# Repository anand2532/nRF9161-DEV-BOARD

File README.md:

# nRF9161 UART Modem Module (v2)

A small 50 × 37.5 mm LTE-M / NB-IoT + GNSS modem board built around the Nordic **nRF9161**. Any host MCU controls it with AT commands over one 10-pin UART header.

> **Status:** v2 has passed DRC (0 errors, 0 unconnected), ERC (0 errors), schematic parity, an RF review and a DFM review. The JLCPCB fab and assembly package is in `fab/staging-v2-36d8578/`. **It has not been ordered yet.**

## Features

- **Nordic nRF9161-LACA-R7** SiP: LTE-M and NB-IoT, plus GNSS. (The nRF9161 has **no 2G/GSM**.)
- **Host interface on one header:** J20 is a 1×10, 2.54 mm header carrying UART with RTS/CTS, DTR wake, RI indicate and an open-drain reset.
- **Level-shifted host side:** SN74LXC translators referenced to the host's VIO (1.1–5.5 V per the LXC range), so 1.8 V, 3.3 V and 5 V hosts all work. If VIO is missing, the translators go hi-Z, so the board never back-powers the host.
- **Single supply:** VIN 3.0–5.5 V. It has reverse-polarity protection (SS34), a TVS (SMAJ5.0A), a 2 A fuse and ferrite filtering, plus a TLV73333 3.3 V LDO for the GPIO and translator rail.
- **nano-SIM (4FF)**, JAE SF72S006, with TPD3F303 ESD protection.
- **Two U.FL connectors:** LTE (J2) and GNSS (J5). The GNSS port supplies bias for an active antenna, switched by a TPS22919 from COEX0.
- **SWD:** 10-pin 1.27 mm Cortex debug header (J8), reset button SW2, and status LEDs (D3 power, D4 status/network).
- **Build:** 4-layer board, 1.6 mm, ENIG, parts on both sides (51 top / 16 bottom). Every part has an LCSC number for JLCPCB assembly.

## Block diagram

```mermaid
flowchart LR
  HOST["Host MCU<br/>(1.8 / 3.3 / 5 V)"] -- "J20: TX RX RTS CTS DTR RI" --> LS["SN74LXC2T45 ×2<br/>SN74LXC1T45 ×2<br/>(VIO ↔ 3.3 V)"]
  HOST -- "J20: nRESET" --> Q1["Q1 BSS138<br/>open-drain"]
  LS --> U1["nRF9161-LACA-R7<br/>LTE-M / NB-IoT / GNSS"]
  Q1 --> U1
  VIN["J20 VIN 3.0–5.5 V"] --> PROT["D1 SS34 · D2 SMAJ5.0A<br/>F1 2 A · FB4"] --> U1
  PROT --> LDO["U2 TLV73333<br/>3.3 V VDD_GPIO"] --> LS
  U1 -- "SIM_RST/CLK/IO/1V8" --> ESD["U4 TPD3F303"] --> SIM["J7 nano-SIM"]
  U1 -- "ANT" --> J2["J2 U.FL LTE"]
  U1 -- "GPS" --> J5["J5 U.FL GNSS"]
  LDO --> SW["U3 TPS22919<br/>(COEX0)"] -- "active-antenna bias" --> J5
  SWD["J8 SWD 2×5 1.27 mm"] --- U1
  U1 -- "P0.00" --> D4["D4 status / network LED"]
```

## Host header J20 pinout

| Pin | Name | Direction (host view) | Modem side |
|---|---|---|---|
| 1 | VIN | power in | 3.0–5.5 V supply |
| 2 | GND | — | ground |
| 3 | VIO | reference in | host logic rail, 1.1–5.5 V (feeds the translators; **not** an output) |
| 4 | TX | host → modem | P0.03, UART RXD (via U5) |
| 5 | RX | modem → host | P0.02, UART TXD (via U6) |
| 6 | RTS | host → modem | P0.07, modem CTS (via U5) |
| 7 | CTS | modem → host | P0.06, modem RTS (via U6) |
| 8 | DTR | host → modem, active-low | P0.31 (via U7, 100k pull-up to VIO) |
| 9 | RI | modem → host, active-low | P0.30 (via U8) |
| 10 | nRESET | host → modem, active-low | open-drain through Q1 BSS138 (5 V safe) |

The RTS/CTS crossover is done on the board, so **wire J20 straight across to the host pins with the same names**. Full details: [`docs/PINOUT.md`](docs/PINOUT.md).

### Host wiring example (3.3 V MCU)

```
Host MCU            J20
3V3 / 5V  ───────── 1 VIN   (must supply ~500 mA LTE TX peaks)
GND       ───────── 2 GND
3V3 (IO)  ───────── 3 VIO
UART TX   ───────── 4 TX
UART RX   ───────── 5 RX
UART RTS  ───────── 6 RTS
UART CTS  ───────── 7 CTS
GPIO (out)───────── 8 DTR   (optional; pull low to wake)
GPIO (in) ───────── 9 RI    (optional)
GPIO (OD) ───────── 10 nRESET (optional)
```

UART settings: 115200 baud, 8N1, hardware flow control (as in the Serial Modem `external-mcu.overlay`).

## Specifications

| Parameter | Value |
|---|---|
| Modem | nRF9161-LACA-R7 (LTE-M, NB-IoT, GNSS) |
| Supply (VIN) | 3.0–5.5 V. Input TVS is 5.0 V; 2 A fuse |
| Host logic (VIO) | 1.1–5.5 V (SN74LXC range) |
| Internal GPIO rail | 3.3 V (TLV73333) |
| Peak current | about 500 mA on LTE TX (VDD2). Use a 1 A-limited supply for bring-up |
| Host UART | 115200 baud, RTS/CTS, DTR, RI |
| Antennas | U.FL LTE (J2); U.FL GNSS, active antenna (J5) |
| SIM | nano-SIM 4FF (JAE SF72S006) |
| Debug | SWD, 2×5 1.27 mm (J8) |
| Board size | 50.05 × 37.55 mm, R2.0 corners |
| PCB | 4 layers, 1.6 mm FR4, ENIG, 1 oz; stackup 0.12 / 1.2 / 0.12 mm |
| Vias | 30 epoxy-filled and capped (POFV) per board: 21 × 0.20 mm, 9 × 0.25 mm |
| Assembly | double-sided: 51 top, 16 bottom (67 parts) |

## Key components

| Ref | Part | Function | LCSC |
|---|---|---|---|
| U1 | NRF9161-LACA-R7 | LTE-M / NB-IoT / GNSS SiP | C21547412 |
| U2 | TLV73333PDBV | 3.3 V LDO (VDD_GPIO) | C134139 |
| U3 | TPS22919DCKR | GNSS active-antenna bias switch | C2149796 |
| U4 | TPD3F303DPV | SIM ESD protection | C2865991 |
| U5, U6 | SN74LXC2T45 | UART level shifters | C5217891 |
| U7, U8 | SN74LXC1T45 | DTR / RI level shifters | C4364198 |
| Q1 | BSS138 | open-drain reset isolator | C52895 |
| D1 | SS34 | reverse-polarity Schottky | C8678 |
| D2 | SMAJ5.0A | VIN TVS | C10758 |
| F1 | 2 A 1206 fuse | input fuse | C187611 |
| J2, J5 | Hirose U.FL-R-SMT-1(10) | LTE / GNSS antenna | C88373 |
| J7 | JAE SF72S006 | nano-SIM holder | C2977286 |
| J8 | 2×5 1.27 mm SMD header | SWD | C5155080 |
| J20 | 1×10 2.54 mm header | host interface | C57369 |
| SW2 | C&K KXT3 | reset button | C778127 |
| D3, D4 | LTST-C191KGKT green 0603 | power / status LEDs | C125098 |

Full BOM and placement: [`jlc/BOM_JLC_v2.csv`](jlc/BOM_JLC_v2.csv), [`jlc/CPL_JLC_v2.csv`](jlc/CPL_JLC_v2.csv), master [`jlc/BOM.csv`](jlc/BOM.csv).

## Board images

| Top | Bottom |
|---|---|
|  |  |
|  |  |

## Getting started

1. **Power up carefully.** Apply 3.3–5.0 V on J20.1 from a current-limited supply. Start around 200 mA, then raise it to 1 A. D3 lights on VIN. Check TP15 VIN, TP14 VDD_nRF, TP13 VDD_GPIO (~3.3 V) and TP17 ENABLE.
2. **SIM.** Insert a nano-SIM. **JP2 (bottom) must be solder-bridged**, or the SIM has no power.
3. **Antennas.** LTE on J2: use a ground-independent antenna (sleeve or flex dipole, 698–2200 MHz), because the small board can't act as a counterpoise for a monopole. GNSS on J5: use an **active** patch antenna.
4. **Flash firmware over SWD.** Build Nordic's [Serial Modem add-on](https://github.com/nrfconnect/ncs-serial-modem) (NCS 3.x) for `nrf9161dk/nrf9161/ns` with the external-MCU overlay, which matches this board's pins with no changes:
   ```sh
   west build -b nrf9161dk/nrf9161/ns app -- -DEXTRA_DTC_OVERLAY_FILE=external-mcu.overlay
   west flash   # J-Link on J8
   # or: nrfjprog -f NRF91 --program merged.hex --chiperase --verify --reset
   ```
   The nRF9161 modem firmware must also be present; flash it with nRF Connect Programmer if needed.
5. **Talk to it** from the host at 115200 baud, RTS/CTS:
   ```
   AT                 -> OK
   AT+CGMR            -> modem firmware version
   AT+CFUN=1          -> radio on
   AT+CEREG=5         -> enable registration notifications
   AT+CEREG?          -> +CEREG: 5,1,... (1 = home, 5 = roaming)
   AT%XMONITOR        -> network/cell info
   AT+CFUN=0          -> radio off
   ```

### Network LED (D4)

D4 sits on **P0.00** (through R10, 1 kΩ, active-high). The Serial Modem app has no built-in network LED, so add about 20 lines of app code: subscribe to LTE registration events and drive P0.00 high on *registered home/roaming*, low otherwise. No hardware change is needed. In the board overlay, define a `gpio-leds` node on `&gpio0 0 GPIO_ACTIVE_HIGH` and disable the unused nRF9161 DK `led0–3` and button nodes.

### Notes

- If you use a passive GNSS antenna, disable the GNSS LNA bias (COEX0, `AT%XCOEX0`).
- SIM_DET (pin 45) intentionally floats. Card detect is on the J7 switch, not on pin 45.
- The LTE π-match (L1 = 0 Ω, C21/C22 DNP) is a placeholder. Tune it with a VNA on the final mechanics.

## Fabrication and ordering (JLCPCB)

Order the **panel**: `fab/staging-v2-36d8578/nRF9161-v2-panel-36d8578.zip`, a 2×2 panel of 118.10 × 93.10 mm with mouse-bite tabs, a 6 mm frame and fiducials. The full instructions are in [`fab/staging-v2-36d8578/ORDER_NOTES.md`](fab/staging-v2-36d8578/ORDER_NOTES.md) and [`docs/FAB_READY_CHECKLIST_V2.md`](docs/FAB_READY_CHECKLIST_V2.md).

- **PCB:** 4 layers, 1.6 mm, ENIG, impedance stackup 0.12 / 1.2 / 0.12 mm.
- **Via filling:** epoxy filled and copper capped (POFV, IPC-4761 Type VII). That's 30 vias per board and 120 per panel, all 0.20 mm and 0.25 mm holes. The caps must be flush or recessed.
- **Assembly:** Standard PCBA, double-sided. Use separate top and bottom 0.10 mm stencils. Reflow the bottom first. U1 paste should be 70–85% of pad area, and U1 needs a first-article X-ray. JP2 is hand-bridged after reflow. J20 is THT and needs selective/wave soldering with a fixture.
- **Rotations:** check them in JLC's DFM preview (U1, U4, U2/U3/U5–U8, Q1, D1–D4, F1, J2/J5, J7, J8, J20, SW2). No offsets are pre-applied.
- **Consign the nRF9161.** JLC listed only 6 in stock for C21547412, so consign U1 or buy it from Mouser or DigiKey.
- **Before ordering,** settle quote questions Q1–Q17 in the checklist (filled-via price, 0.20 mm drill in 1.6 mm, JP2 bridge, J20 fixture, panel CPL designators, mouse-bite minimum).

## Where to buy in India

JLC assembly uses the LCSC parts in `jlc/`. Indian sourcing is for **hand assembly, rework or spares**. See **[india/README.md](india/README.md)** for Indian PCB fab and assembly vendors (with which ones can likely make the 0.20 mm filled vias) and for component vendors. The per-part sourcing list is [india/BOM_INDIA.csv](india/BOM_INDIA.csv) (Robu, then LionCircuits, with URLs, INR prices and stock).

## Repository structure

```
.
├── README.md
├── hardware/                 KiCad 9 project (open hardware/nRF9161-DEV-BOARD.kicad_pro)
│   ├── nRF9161-DEV-BOARD.kicad_{pro,pcb,sch,dru,prl}
│   ├── schematic/            hierarchical sheets 01–12
│   ├── libraries/            project symbols + footprints (Board.pretty, Nordic_*)
│   ├── 3dmodels/             placeholder STEP models
│   ├── panel/                2×2 JLC panel project
│   └── fp-lib-table, sym-lib-table   (${KIPRJMOD}-relative)
├── jlc/                      BOM_JLC_v2.csv, CPL_JLC_v2.csv, master BOM.csv
├── india/                    India sourcing: BOM_INDIA.csv/.xlsx, fab + parts vendor guide
├── fab/
│   ├── staging-v2-36d8578/   current fab package (single + panel zips, ORDER_NOTES)
│   └── archive/              older staging packages and v1 outputs
├── docs/                     pinout, fab checklist, stackup, reviews
│   └── reports/              design, RF, DFM and DRC/ERC reports
├── images/                   renders and assembly drawings
└── tools/                    helper scripts
```

## Revision history

| Version | Branch | Notes |
|---|---|---|
| v1 | [`v1-dev-board`](../../tree/v1-dev-board) | Full breakout development board (120 × 80 mm, many headers) |
| v2 | `main` | UART modem module: breakouts removed, single J20 host header with level shifters, 50.05 × 37.55 mm, double-sided assembly, U4 DPV footprint fixed, JLC-ready |

## References

- nRF9161 Product Specification, nRF91 Hardware Design Guidelines, nWP033 (antenna/RF), nWP054 (footprint)
- nRF9161 DK PCA10153 reference design
- [Nordic Serial Modem add-on](https://github.com/nrfconnect/ncs-serial-modem)

## License

This hardware design is licensed under the **CERN Open Hardware Licence Version 2 – Permissive (CERN-OHL-P v2)**. See [LICENSE](LICENSE) for the full text.

Copyright 2026 Anand Mohan Pandey. SPDX-License-Identifier: CERN-OHL-P-2.0

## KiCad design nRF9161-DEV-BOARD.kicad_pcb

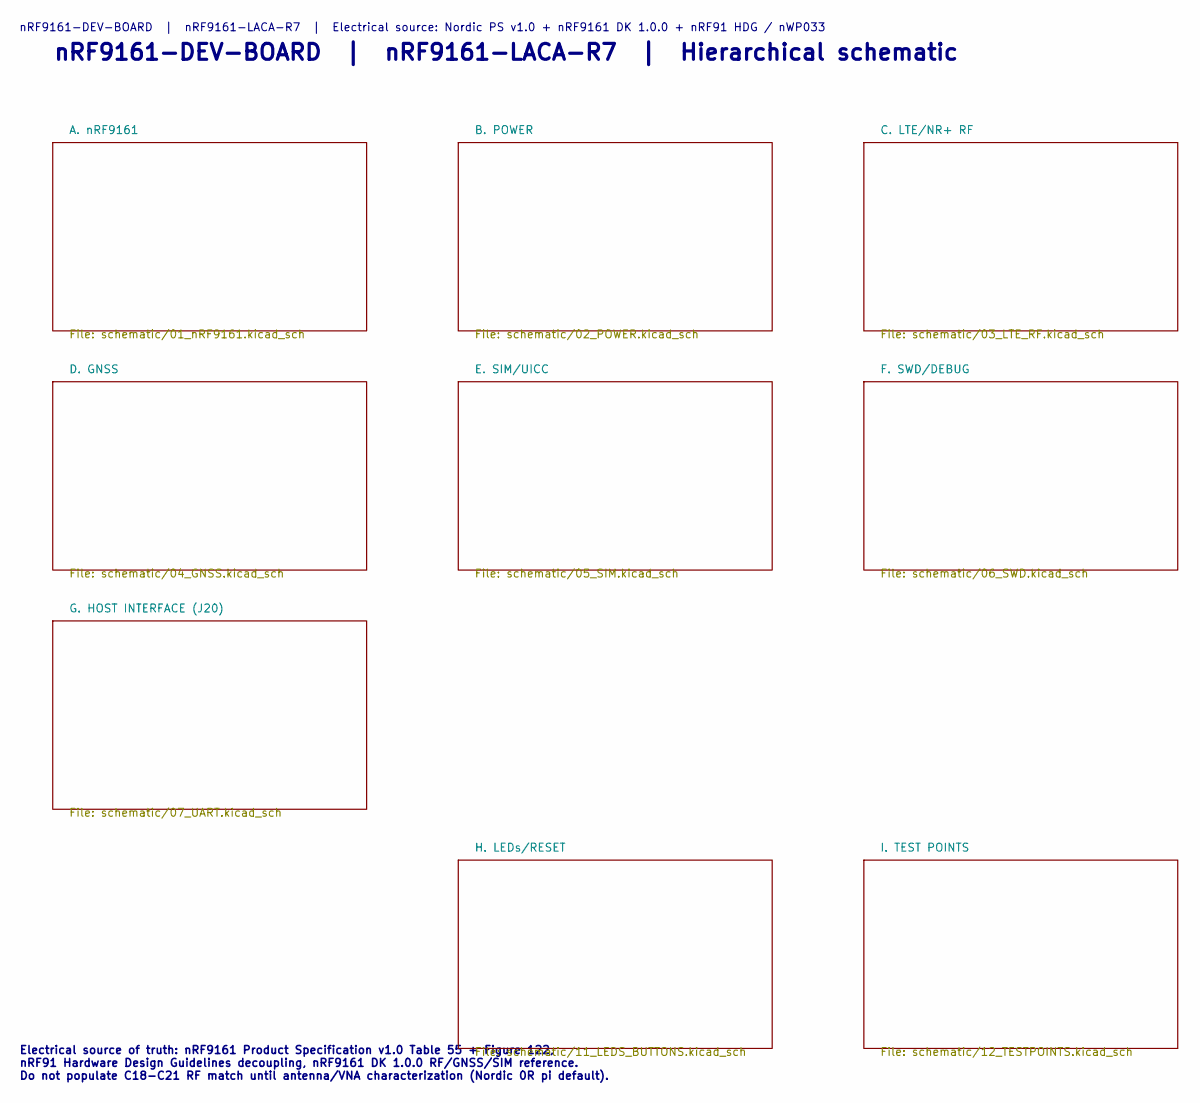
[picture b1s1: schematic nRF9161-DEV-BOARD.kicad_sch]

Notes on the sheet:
nRF9161-DEV-BOARD | nRF9161-LACA-R7 | Electrical source: Nordic PS v1.0 + nRF9161 DK 1.0.0 + nRF91 HDG / nWP033
nRF9161-DEV-BOARD | nRF9161-LACA-R7 | Hierarchical schematic
Electrical source of truth: nRF9161 Product Specification v1.0 Table 55 + Figure 122, nRF91 Hardware Design Guidelines decoupling, nRF9161 DK 1.0.0 RF/GNSS/SIM reference. Do not populate C18-C21 RF match until antenna/VNA characterization (Nordic 0R pi default).

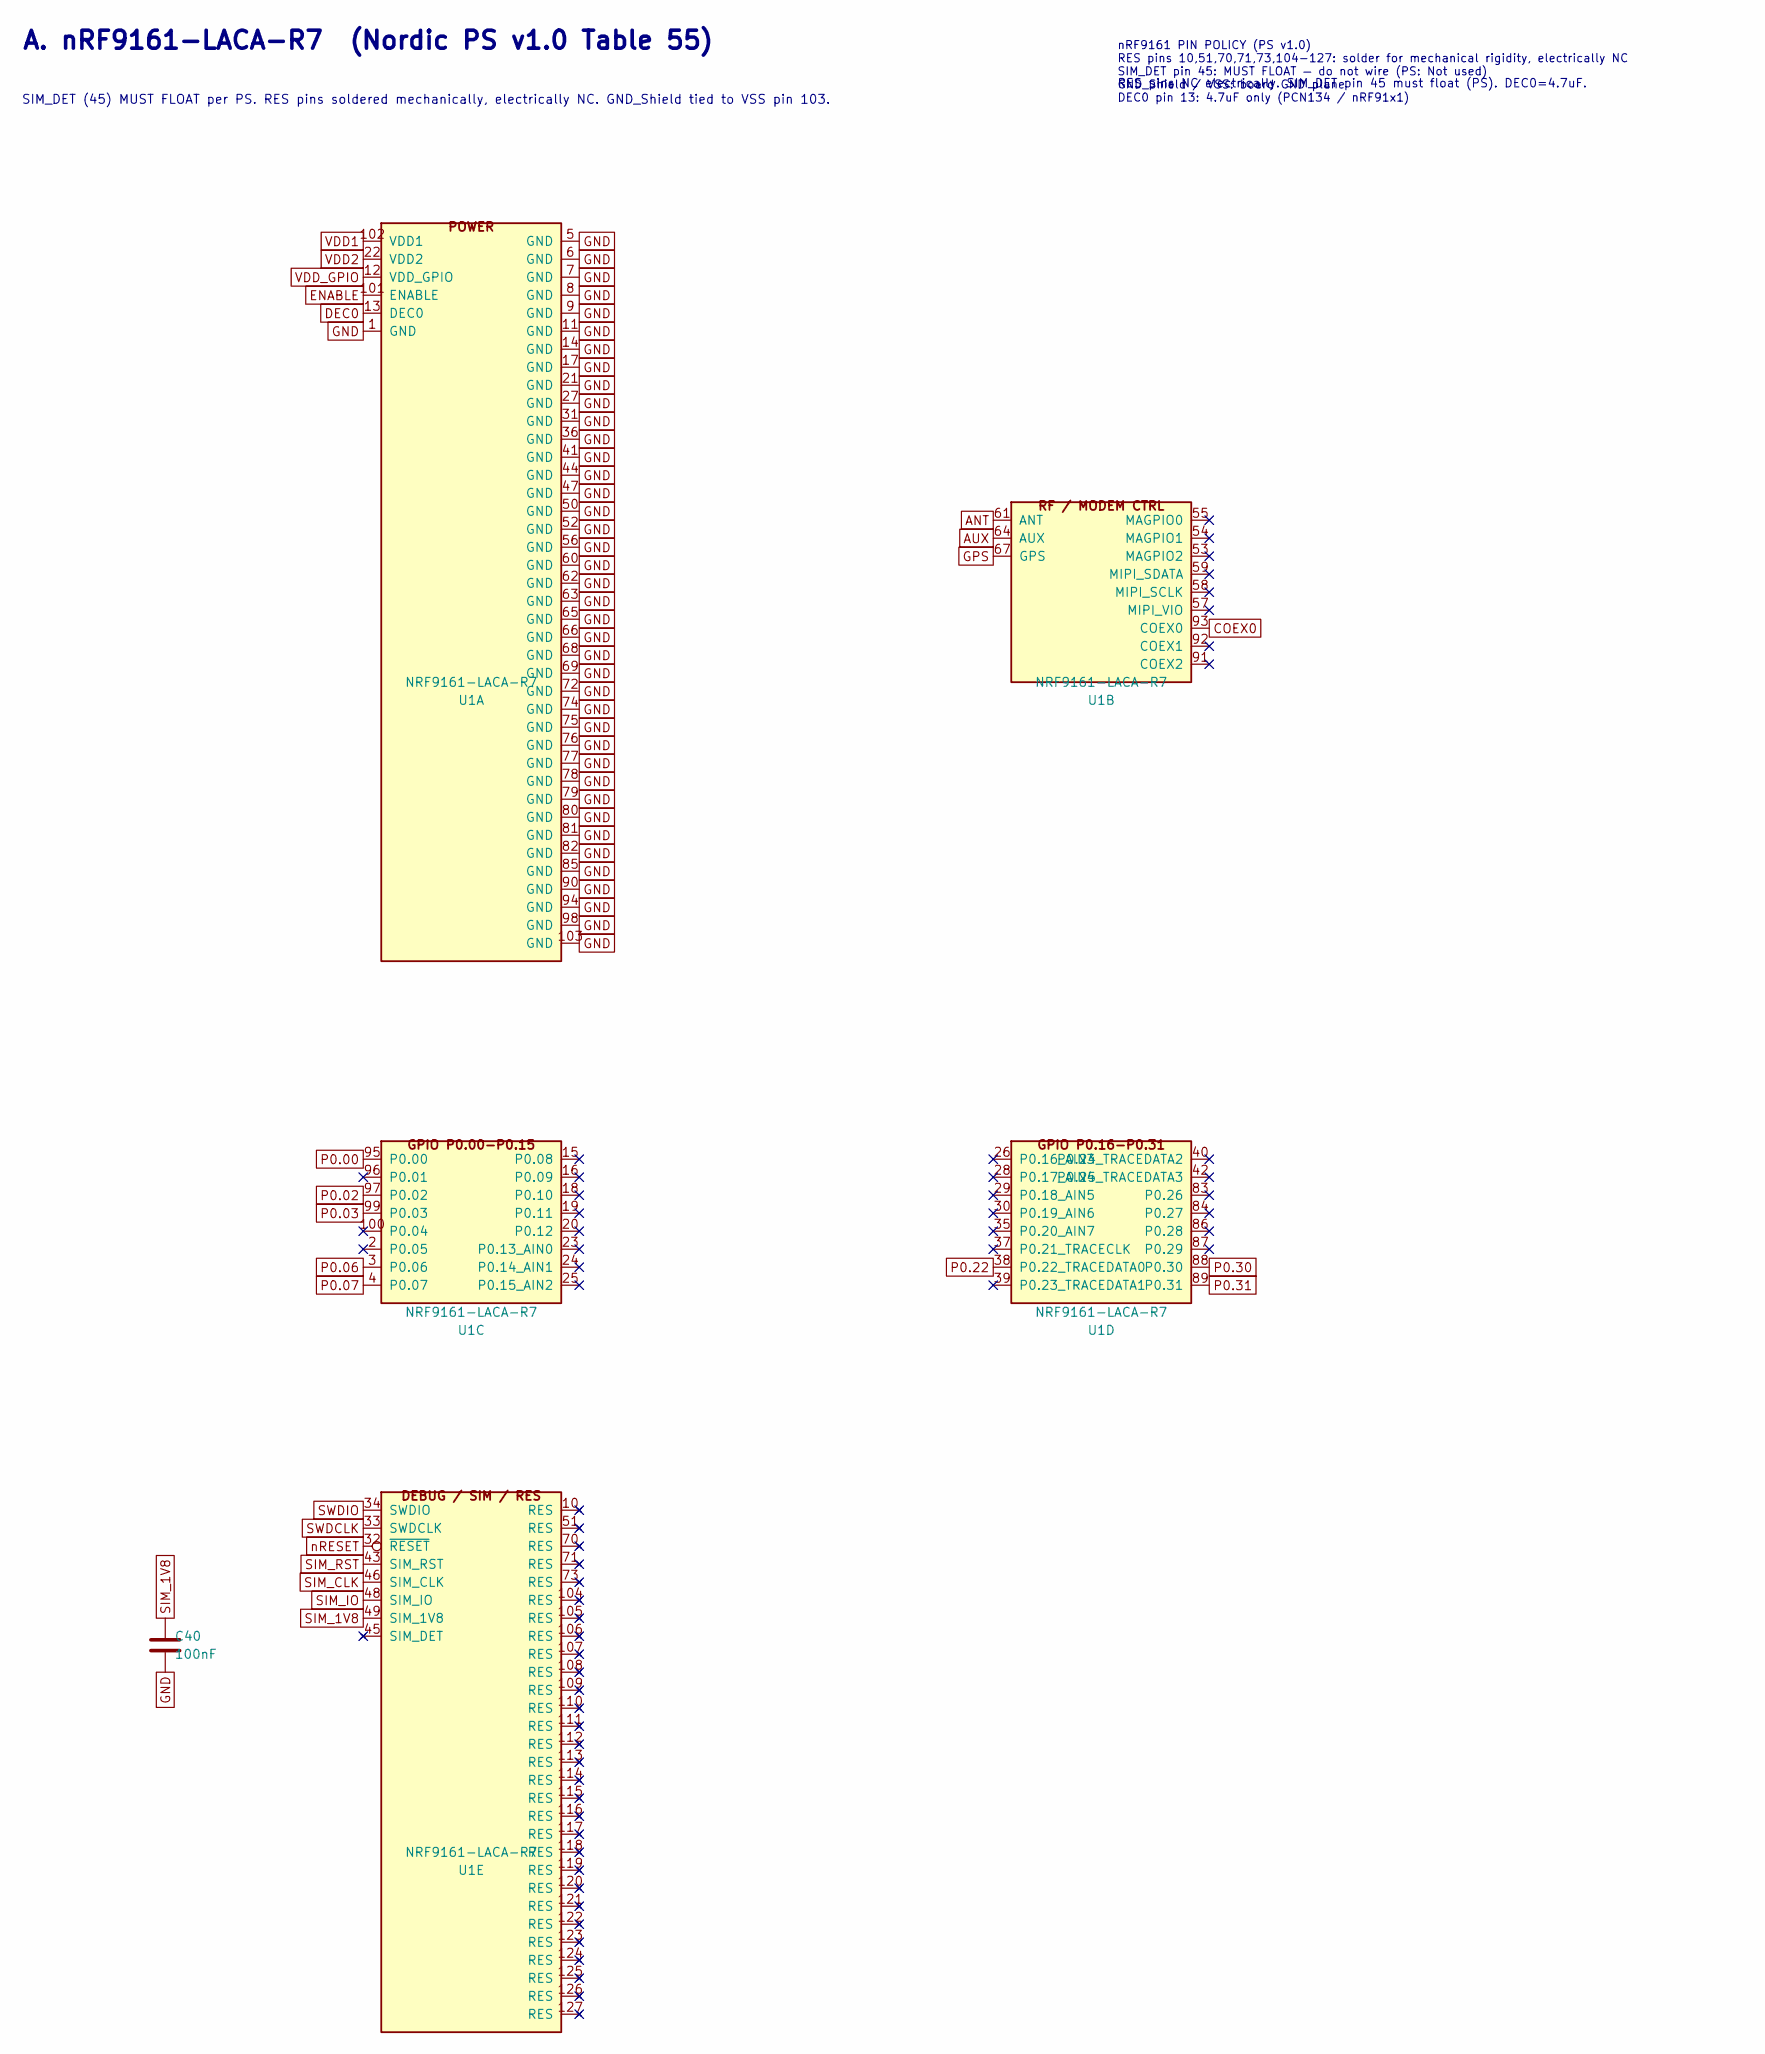
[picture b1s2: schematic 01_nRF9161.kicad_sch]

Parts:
C40: 100nF; C_0402_1005Metric; MPN GRM155R71A104KA01D; LCSC C71687
U1: NRF9161-LACA-R7; nRF9161_LGA_16.0x10.5mm; MPN NRF9161-LACA-R7; LCSC C21547412

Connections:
ANT: U1.61 (ANT); also elsewhere on the board
AUX: U1.64 (AUX); also elsewhere on the board
COEX0: U1.93 (COEX0); also elsewhere on the board
DEC0: U1.13 (DEC0); also elsewhere on the board
ENABLE: U1.101 (ENABLE); also elsewhere on the board
GND: C40.2, U1.1 (GND), U1.5 (GND), U1.6 (GND), U1.7 (GND), U1.8 (GND), U1.9 (GND), U1.11 (GND), U1.14 (GND), U1.17 (GND), U1.21 (GND), U1.27 (GND), U1.31 (GND), U1.36 (GND), U1.41 (GND), U1.44 (GND), U1.47 (GND), U1.50 (GND), U1.52 (GND), U1.56 (GND), U1.60 (GND), U1.62 (GND), U1.63 (GND), U1.65 (GND), U1.66 (GND), U1.68 (GND), U1.69 (GND), U1.72 (GND), U1.74 (GND), U1.75 (GND), U1.76 (GND), U1.77 (GND), U1.78 (GND), U1.79 (GND), U1.80 (GND), U1.81 (GND), U1.82 (GND), U1.85 (GND), U1.90 (GND), U1.94 (GND), U1.98 (GND), U1.103 (GND); also elsewhere on the board
GPS: U1.67 (GPS); also elsewhere on the board
P0.00: U1.95 (P0.00); also elsewhere on the board
P0.02: U1.97 (P0.02); also elsewhere on the board
P0.03: U1.99 (P0.03); also elsewhere on the board
P0.06: U1.3 (P0.06); also elsewhere on the board
P0.07: U1.4 (P0.07); also elsewhere on the board
P0.22: U1.38 (P0.22_TRACEDATA0); also elsewhere on the board
P0.30: U1.88 (P0.30); also elsewhere on the board
P0.31: U1.89 (P0.31); also elsewhere on the board
SIM_1V8: C40.1, U1.49 (SIM_1V8); also elsewhere on the board
SIM_CLK: U1.46 (SIM_CLK); also elsewhere on the board
SIM_IO: U1.48 (SIM_IO); also elsewhere on the board
SIM_RST: U1.43 (SIM_RST); also elsewhere on the board
SWDCLK: U1.33 (SWDCLK); also elsewhere on the board
SWDIO: U1.34 (SWDIO); also elsewhere on the board
VDD1: U1.102 (VDD1); also elsewhere on the board
VDD2: U1.22 (VDD2); also elsewhere on the board
VDD_GPIO: U1.12 (VDD_GPIO); also elsewhere on the board
nRESET: U1.32 (~RESET); also elsewhere on the board

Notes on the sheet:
A. nRF9161-LACA-R7 (Nordic PS v1.0 Table 55)
SIM_DET (45) MUST FLOAT per PS. RES pins soldered mechanically, electrically NC. GND_Shield tied to VSS pin 103.
nRF9161 PIN POLICY (PS v1.0) RES pins 10,51,70,71,73,104-127: solder for mechanical rigidity, electrically NC SIM_DET pin 45: MUST FLOAT — do not wire (PS: Not used) GND_Shield / VSS: board GND plane DEC0 pin 13: 4.7uF only (PCN134 / nRF91x1)
RES pins NC electrically. SIM_DET pin 45 must float (PS). DEC0=4.7uF.

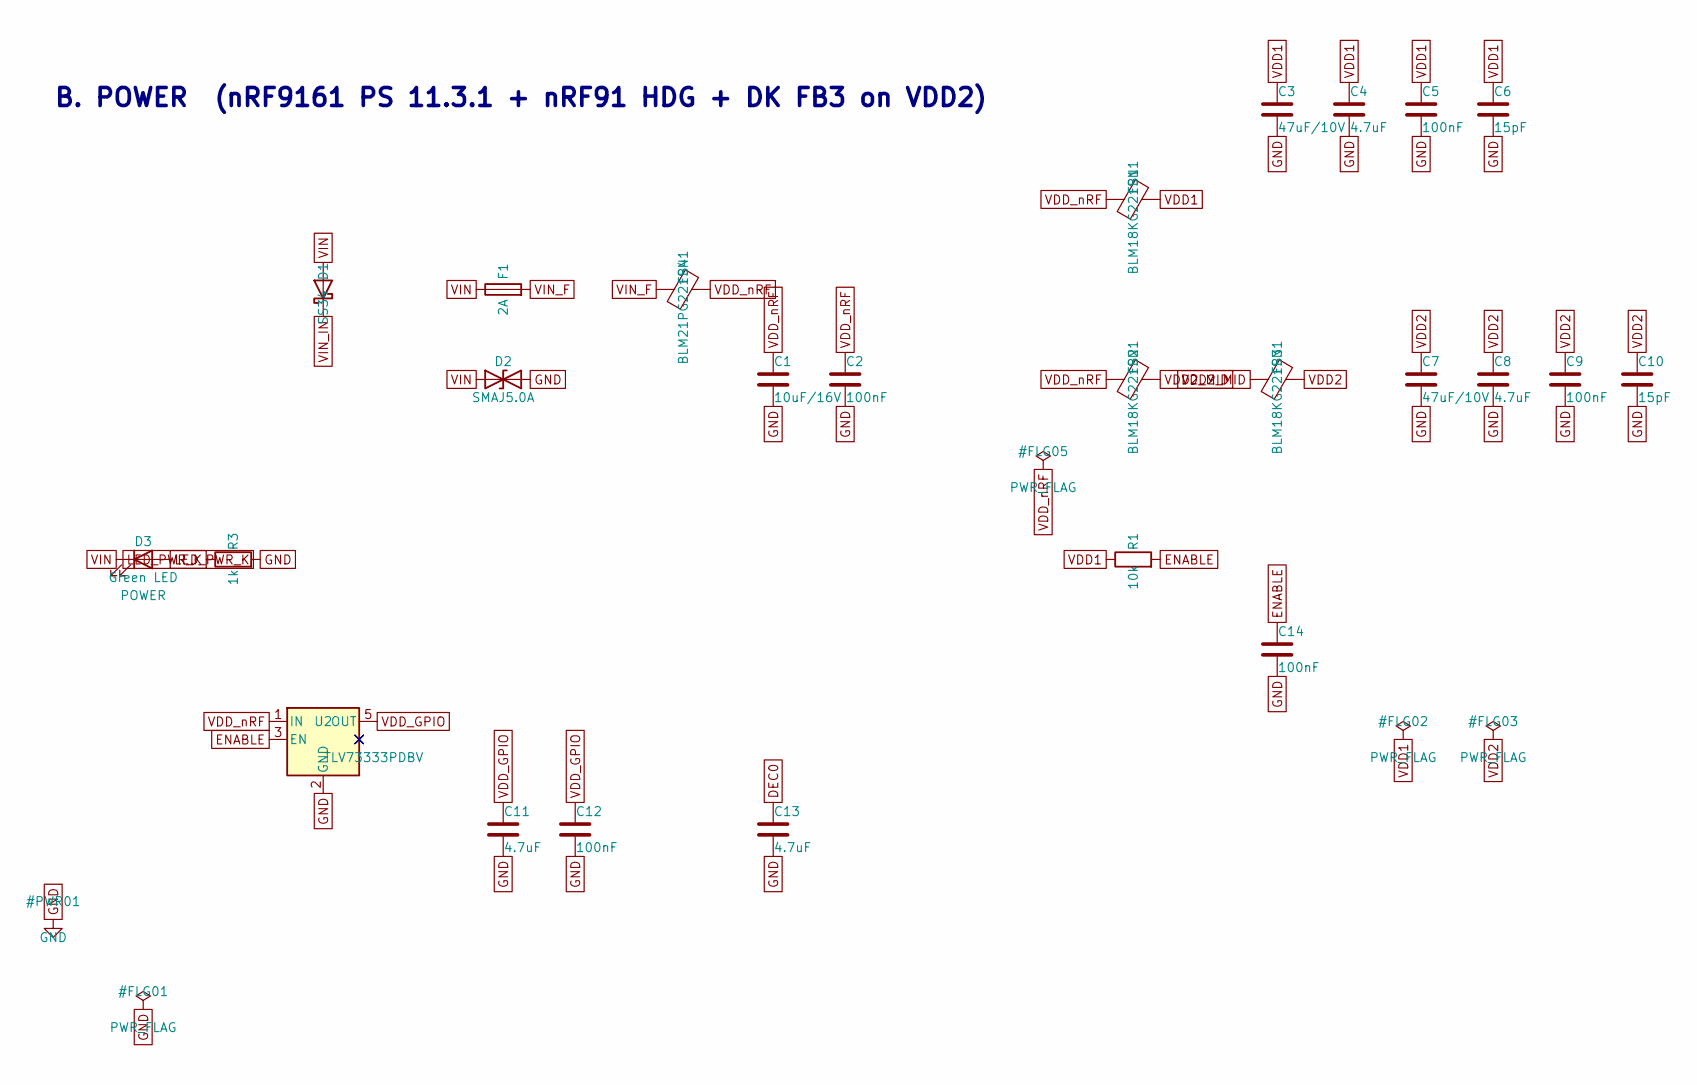
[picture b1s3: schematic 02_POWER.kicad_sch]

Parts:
C1: 10uF/16V; C_0805_2012Metric; MPN CL21A106KOQNNNE; LCSC C1713
C2: 100nF; C_0402_1005Metric; MPN CL05B104KO5NNNC; LCSC C1525
C3, C7: 47uF/10V; C_0805_2012Metric; MPN GRM21BR61A476ME15L; LCSC C124129
C4, C8, C11, C13: 4.7uF; C_0402_1005Metric; MPN GRM155R61A475MEAAD; LCSC C335105
C5, C9, C12, C14: 100nF; C_0201_0603Metric; MPN GRM033R61A104KE15D; LCSC C76934
C6, C10: 15pF; C_0201_0603Metric; MPN GJM0335C1E150JB01D; LCSC C710722
D1: SS34; D_SMA; MPN SS34; LCSC C8678
D2: SMAJ5.0A; D_SMA; MPN SMAJ5.0A; LCSC C10758
D3: Green LED; LED_0603_1608Metric; MPN LTST-C191KGKT; LCSC C125098
F1: 2A; Fuse_1206_3216Metric; MPN 0468002.NRHF; LCSC C187611
FB1, FB2, FB3: BLM18KG221SN1; L_0603_1608Metric; MPN BLM18KG221SN1D; LCSC C88980
FB4: BLM21PG221SN1; L_0805_2012Metric; MPN BLM21PG221SN1D; LCSC C85840
R1: 10k; R_0201_0603Metric; MPN RC0201FR-0710KL; LCSC C106225
R3: 1k; R_0402_1005Metric; MPN 0402WGF1001TCE; LCSC C11702
U2: TLV73333PDBV; SOT-23-5; MPN TLV73333PDBVR; LCSC C134139

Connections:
DEC0: C13.1; also elsewhere on the board
ENABLE: C14.1, R1.2, U2.3 (EN); also elsewhere on the board
GND: C1.2, C2.2, C3.2, C4.2, C5.2, C6.2, C7.2, C8.2, C9.2, C10.2, C11.2, C12.2, C13.2, C14.2, D2.2 (A2), R3.2, U2.2 (GND); also elsewhere on the board
LED_PWR_K: D3.2 (A), R3.1
VDD1: C3.1, C4.1, C5.1, C6.1, FB1.2, R1.1; also elsewhere on the board
VDD2: C7.1, C8.1, C9.1, C10.1, FB3.2; also elsewhere on the board
VDD2_MID: FB2.2, FB3.1
VDD_GPIO: C11.1, C12.1, U2.5 (OUT); also elsewhere on the board
VDD_nRF: C1.1, C2.1, FB1.1, FB2.1, FB4.2, U2.1 (IN); also elsewhere on the board
VIN: D1.2 (A), D2.1 (A1), D3.1 (K), F1.1; also elsewhere on the board
VIN_F: F1.2, FB4.1
VIN_IN: D1.1 (K); also elsewhere on the board

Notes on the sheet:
B. POWER (nRF9161 PS 11.3.1 + nRF91 HDG + DK FB3 on VDD2)

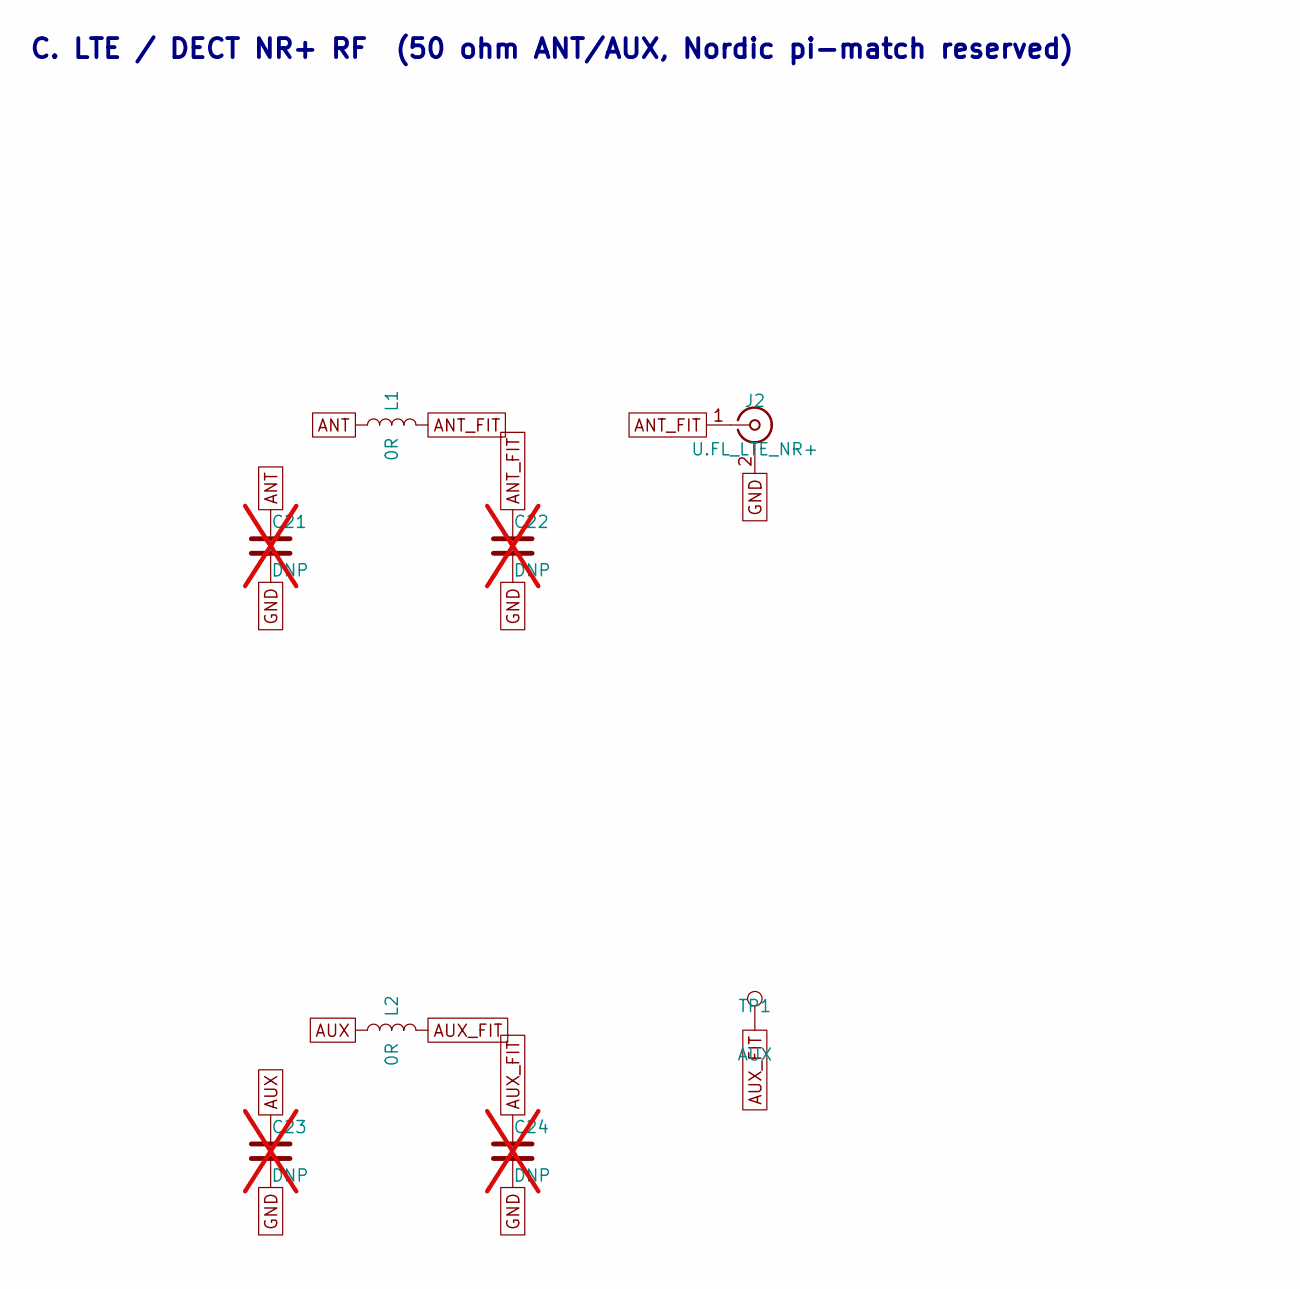
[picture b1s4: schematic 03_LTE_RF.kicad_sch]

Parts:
C21, C22, C23, C24: DNP; C_0402_1005Metric; not fitted
J2: U.FL_LTE_NR+; U.FL_Hirose_U.FL-R-SMT-1_Vertical; MPN U.FL-R-SMT-1(10); LCSC C88373
L1, L2: 0R; L_0402_1005Metric; MPN 0402WGF0000TCE; LCSC C17168
TP1: AUX; TestPoint_Pad_D1.5mm

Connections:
ANT: C21.1, L1.1; also elsewhere on the board
ANT_FIT: C22.1, J2.1 (In), L1.2
AUX: C23.1, L2.1; also elsewhere on the board
AUX_FIT: C24.1, L2.2, TP1.1
GND: C21.2, C22.2, C23.2, C24.2, J2.2 (Ext); also elsewhere on the board

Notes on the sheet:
C. LTE / DECT NR+ RF (50 ohm ANT/AUX, Nordic pi-match reserved)

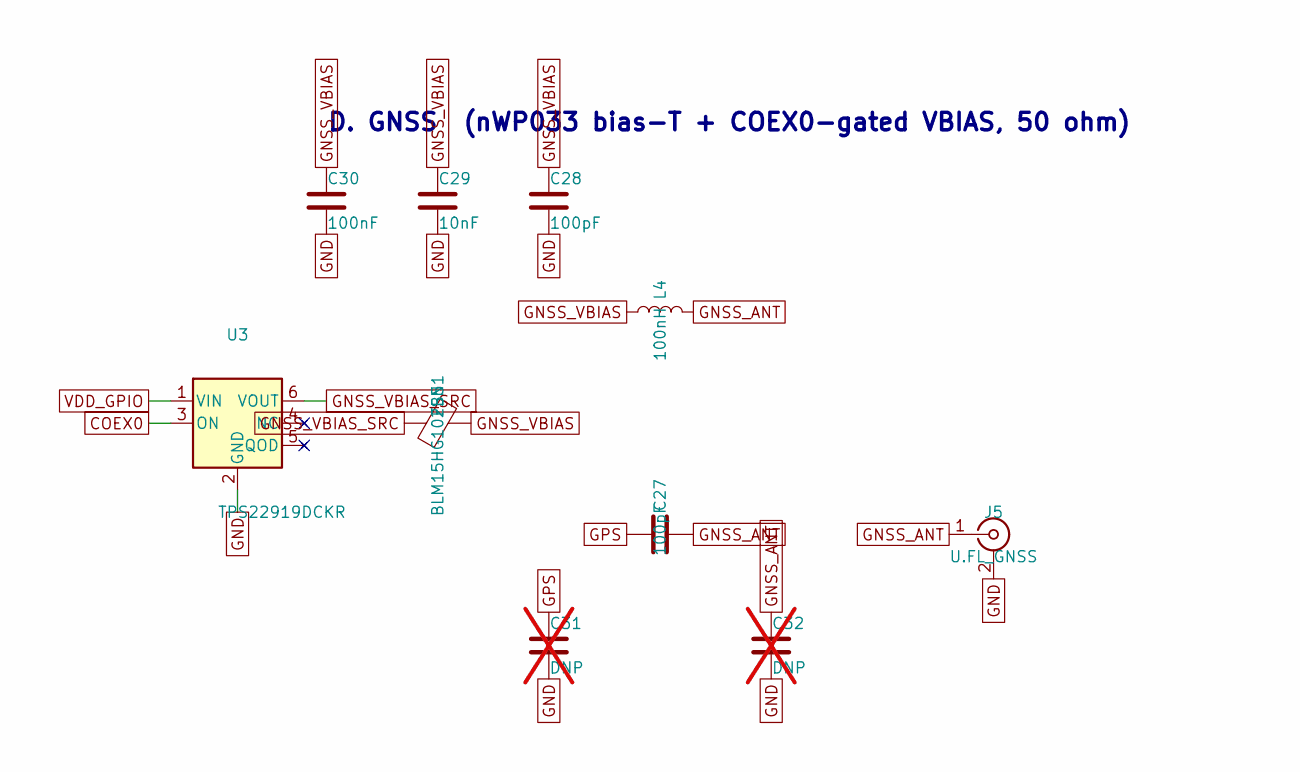
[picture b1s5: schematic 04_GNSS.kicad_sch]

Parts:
C27: 100pF; C_0201_0603Metric; MPN GRM0335C1H101JA01D; LCSC C76922
C28: 100pF; C_0402_1005Metric; MPN GRM1555C1H101JA01D; LCSC C77177
C29: 10nF; C_0402_1005Metric; MPN CL05B103KB5NNNC; LCSC C15195
C30: 100nF; C_0402_1005Metric; MPN CL05B104KO5NNNC; LCSC C1525
C31, C32: DNP; C_0402_1005Metric; not fitted
FB5: BLM15HG102SN1; L_0402_1005Metric; MPN BLM15HG102SN1D; LCSC C76889
J5: U.FL_GNSS; U.FL_Hirose_U.FL-R-SMT-1_Vertical; MPN U.FL-R-SMT-1(10); LCSC C88373
L4: 100nH; L_0402_1005Metric; MPN LQW15ANR10J00D; LCSC C86130
U3: TPS22919DCKR; SOT-363_SC-70-6; MPN TPS22919DCKR; LCSC C2149796

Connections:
COEX0: U3.3 (ON); also elsewhere on the board
GND: C28.2, C29.2, C30.2, C31.2, C32.2, J5.2 (Ext), U3.2 (GND); also elsewhere on the board
GNSS_ANT: C27.2, C32.1, J5.1 (In), L4.2
GNSS_VBIAS: C28.1, C29.1, C30.1, FB5.2, L4.1
GNSS_VBIAS_SRC: FB5.1, U3.6 (VOUT)
GPS: C27.1, C31.1; also elsewhere on the board
VDD_GPIO: U3.1 (VIN); also elsewhere on the board

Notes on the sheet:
D. GNSS (nWP033 bias-T + COEX0-gated VBIAS, 50 ohm)

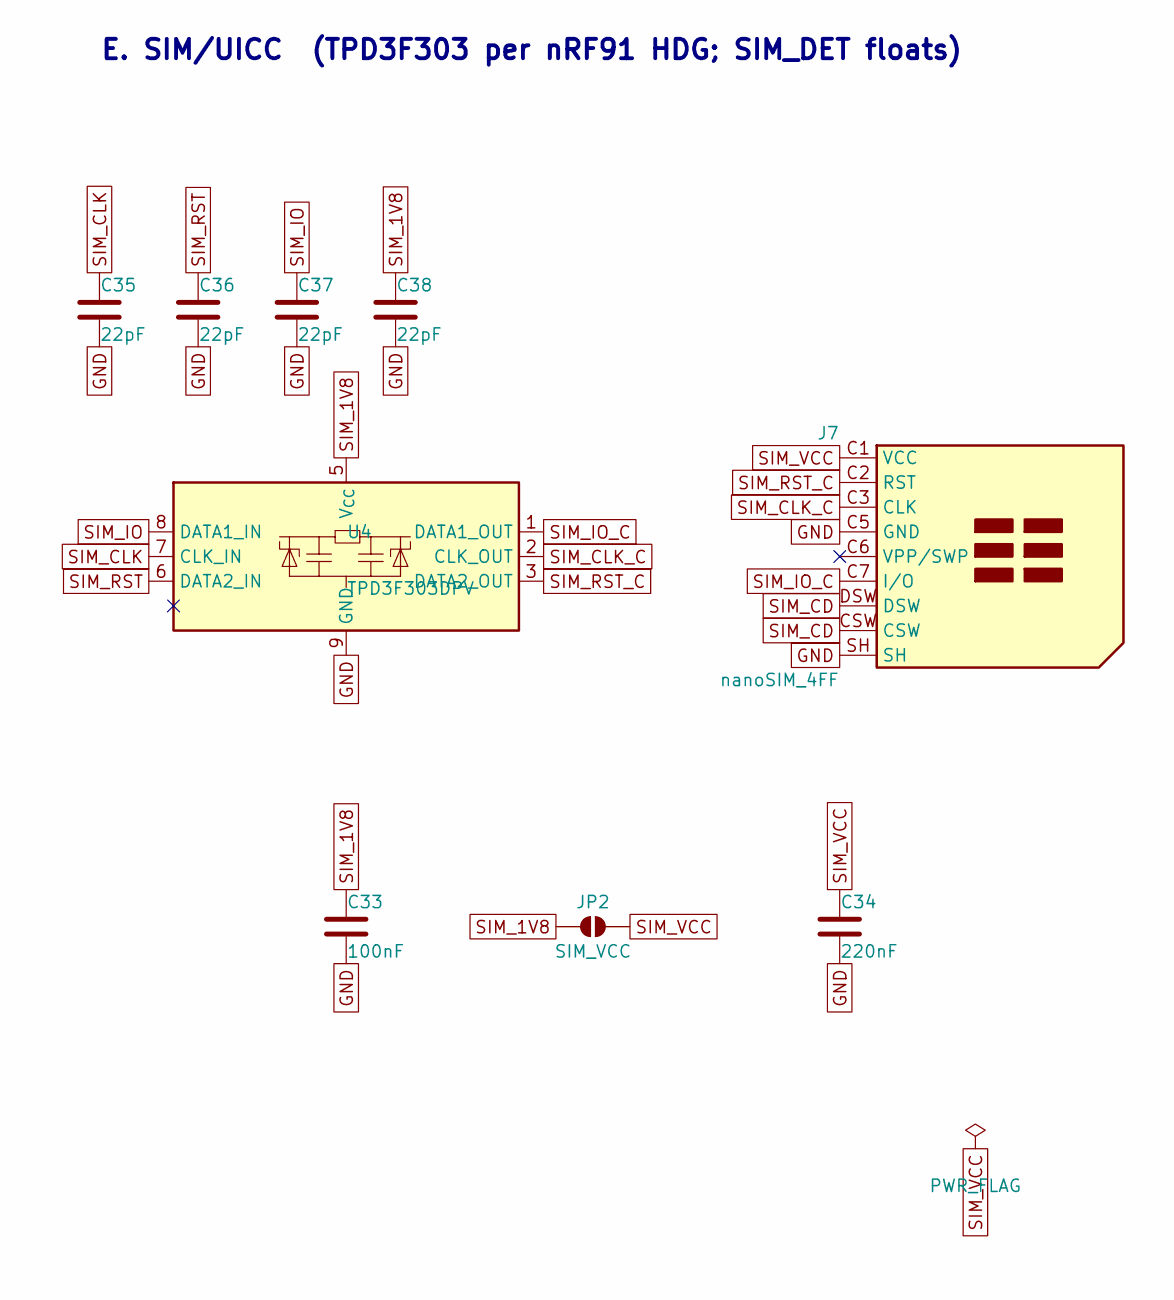
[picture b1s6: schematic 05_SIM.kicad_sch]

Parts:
C33: 100nF; C_0402_1005Metric; MPN CL05B104KO5NNNC; LCSC C1525
C34: 220nF; C_0402_1005Metric; MPN CL05B224KO5NNNC; LCSC C16772
C35, C36, C37, C38: 22pF; C_0201_0603Metric; MPN GRM0335C1H220JA01D; LCSC C76924
J7: nanoSIM_4FF; JAE_SIM_Card_SF72S006; MPN SF72S006VBDR2500; LCSC C2977286
JP2: SIM_VCC; SolderJumper-2_P1.3mm_Open_RoundedPad1.0x1.5mm
U4: TPD3F303DPV; TI_TPD3F303_USON-8_DPV_2.1x1.6mm_P0.5mm; MPN TPD3F303DPVR; LCSC C2865991

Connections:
GND: C33.2, C34.2, C35.2, C36.2, C37.2, C38.2, J7.C5 (GND), J7.SH, U4.9 (GND); also elsewhere on the board
SIM_1V8: C33.1, C38.1, JP2.1 (A), U4.5 (V_{CC}); also elsewhere on the board
SIM_CD: J7.CSW, J7.DSW
SIM_CLK: C35.1, U4.7 (CLK_IN); also elsewhere on the board
SIM_CLK_C: J7.C3 (CLK), U4.2 (CLK_OUT)
SIM_IO: C37.1, U4.8 (DATA1_IN); also elsewhere on the board
SIM_IO_C: J7.C7 (I/O), U4.1 (DATA1_OUT)
SIM_RST: C36.1, U4.6 (DATA2_IN); also elsewhere on the board
SIM_RST_C: J7.C2 (RST), U4.3 (DATA2_OUT)
SIM_VCC: C34.1, J7.C1 (VCC), JP2.2 (B)

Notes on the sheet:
E. SIM/UICC (TPD3F303 per nRF91 HDG; SIM_DET floats)

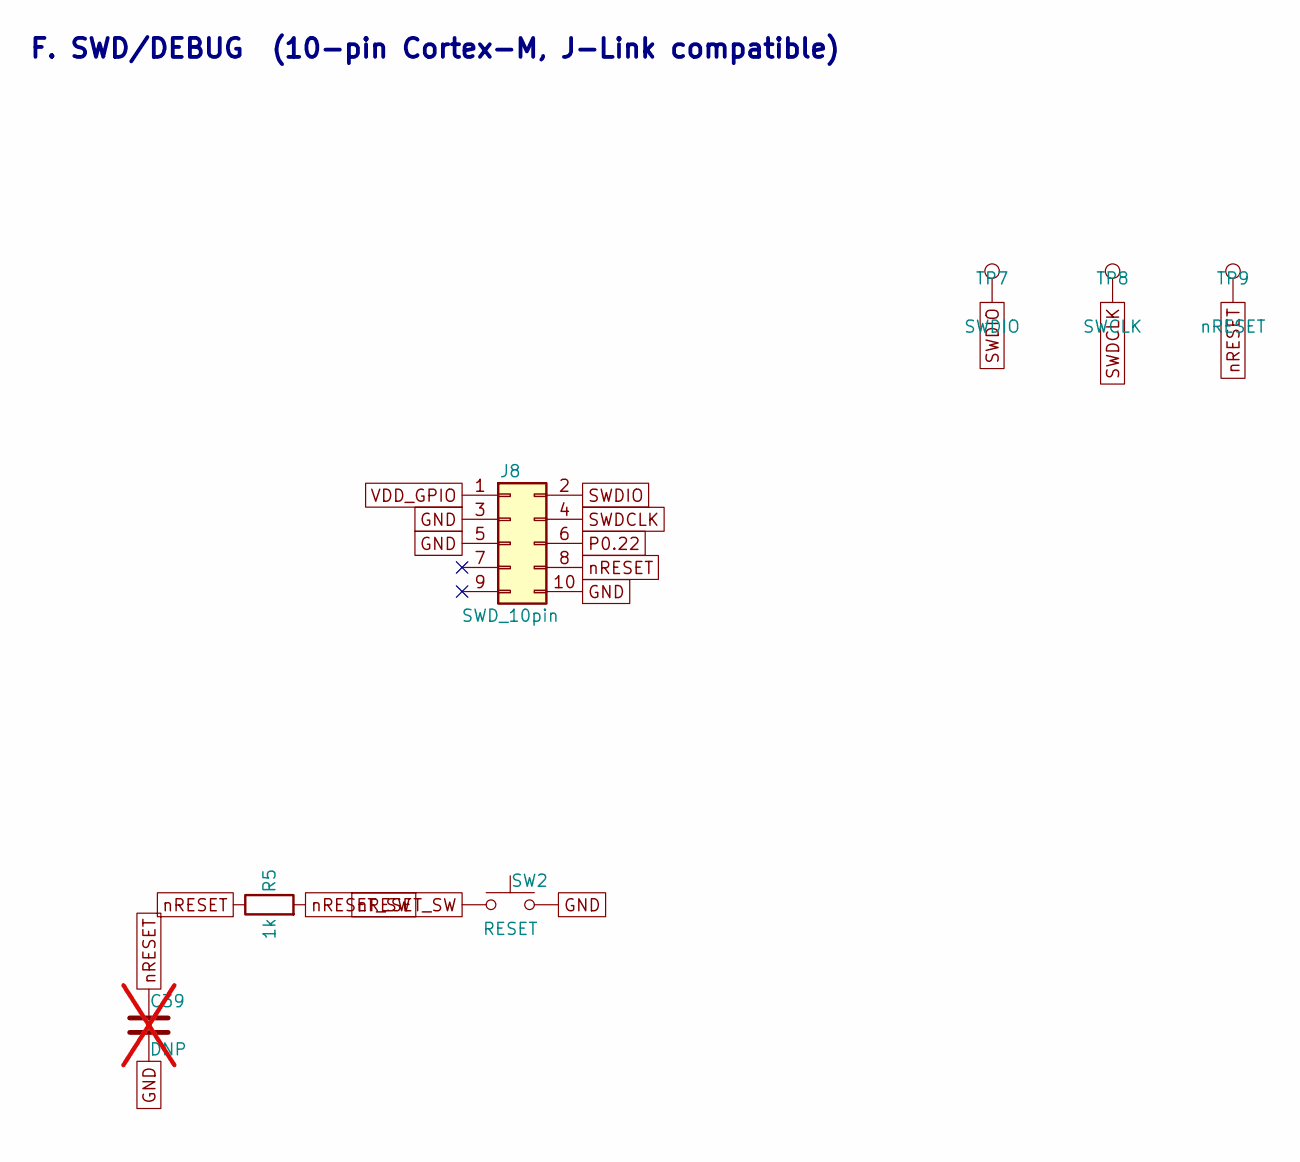
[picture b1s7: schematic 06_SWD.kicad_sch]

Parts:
C39: DNP; C_0201_0603Metric; not fitted
J8: SWD_10pin; PinHeader_2x05_P1.27mm_Vertical_SMD; MPN FTSH-105-01-L-DV-K; LCSC C5155080
R5: 1k; R_0201_0603Metric; MPN RC0201FR-071KL; LCSC C138165
SW2: RESET; SW_SPST_CK_KXT3; MPN KXT331LHS; LCSC C778127
TP7: SWDIO; TestPoint_Pad_D1.5mm
TP8: SWCLK; TestPoint_Pad_D1.5mm
TP9: nRESET; TestPoint_Pad_D1.5mm

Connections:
GND: C39.2, J8.3, J8.5, J8.10, SW2.2; also elsewhere on the board
P0.22: J8.6; also elsewhere on the board
SWDCLK: J8.4, TP8.1; also elsewhere on the board
SWDIO: J8.2, TP7.1; also elsewhere on the board
VDD_GPIO: J8.1; also elsewhere on the board
nRESET: C39.1, J8.8, R5.1, TP9.1; also elsewhere on the board
nRESET_SW: R5.2, SW2.1

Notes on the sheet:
F. SWD/DEBUG (10-pin Cortex-M, J-Link compatible)

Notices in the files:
README.md:
License: CERN-OHL-P-2.0
